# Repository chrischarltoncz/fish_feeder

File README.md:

# fish_feeder

This is the python code to run the pneumatic fish feeder system which functions as follows:

The food is placed in a clear plastic cylinder/hopper. There is an illumination LED strip to light it up on one side. A Pi camera on the opposite side to capture images of the tube and the food. This image will be used for tracking food consumption and level.

The base of the tube has the main feeder body, this incorporates a delrin screw drive to move the food. The screw is rotated via at NEMA17 motor at one end, at the opposite end is an opto sensor and a 6 slot chopper for counting the rotations. This is used to confirm the rotation happens and the motor is not jammed.

The thread deposits the food into a conical volume, this funnels it down to a fitting where it exits the food hopper body/assembly. Above the conical volume is mounted an air solenoid valve, it is fed via 22-25psi house air. The air supply is split off via a needle valve to supply a small continuous stream of air that travels to the bulk food.
This is to keep it dry, it also passes over a temperature and humidity sensor to record the values, this ensures the food is always exposed to dry air and if there is an air supply problem it can be flagged.

Currently (Jan 2025) the air solenoid is turned on prior to the food loading screw rotation, this is to equalize the pressure along the various parts (thread/hopper) so fine powdered food does not flow and collect/jam the screw mech.

Once the food passes out of the food hopper mech, it passes to the rotary valve mechanism.

There is a curved interface tube which is centrally located and passes to near the circumference of a rotating disc, this disc has embedded magnets which lightly clamp the rotor to the stator, the stator underneath has 30X fittings which correspond to each fish tank. 

The rotor is turned via a belt which is in turn rotated via a NEMA23 stepper motor. A home sensor microswitch is stationary on the main feeder assembly, it activates via a 3D printed bump which is VHB taped to the rotor. There is a well defined number of microsteps between home and port 1 so the system can home and index to the correct port location.

One each feeding cycle the rotor is re-homed, then indexed to port 1. Prior to food loading the tank/port is air dried for a number of seconds (typically 60-75) to dry the end of the tube to avoid wet food. 

Links:

Stepper motor drive boards:
https://www.allmotion.com/ezhr17en

Onshape design:
[https://www.allmotion.com/ezhr17en
](https://cad.onshape.com/documents/b092e7b6adc17bd3a3390fe1/w/5d2cf434299dfa3fc55c8225/e/223d4cf3e3f1612e807b6f1d?renderMode=0&uiState=6785ac46c4b3921eef4992e4)

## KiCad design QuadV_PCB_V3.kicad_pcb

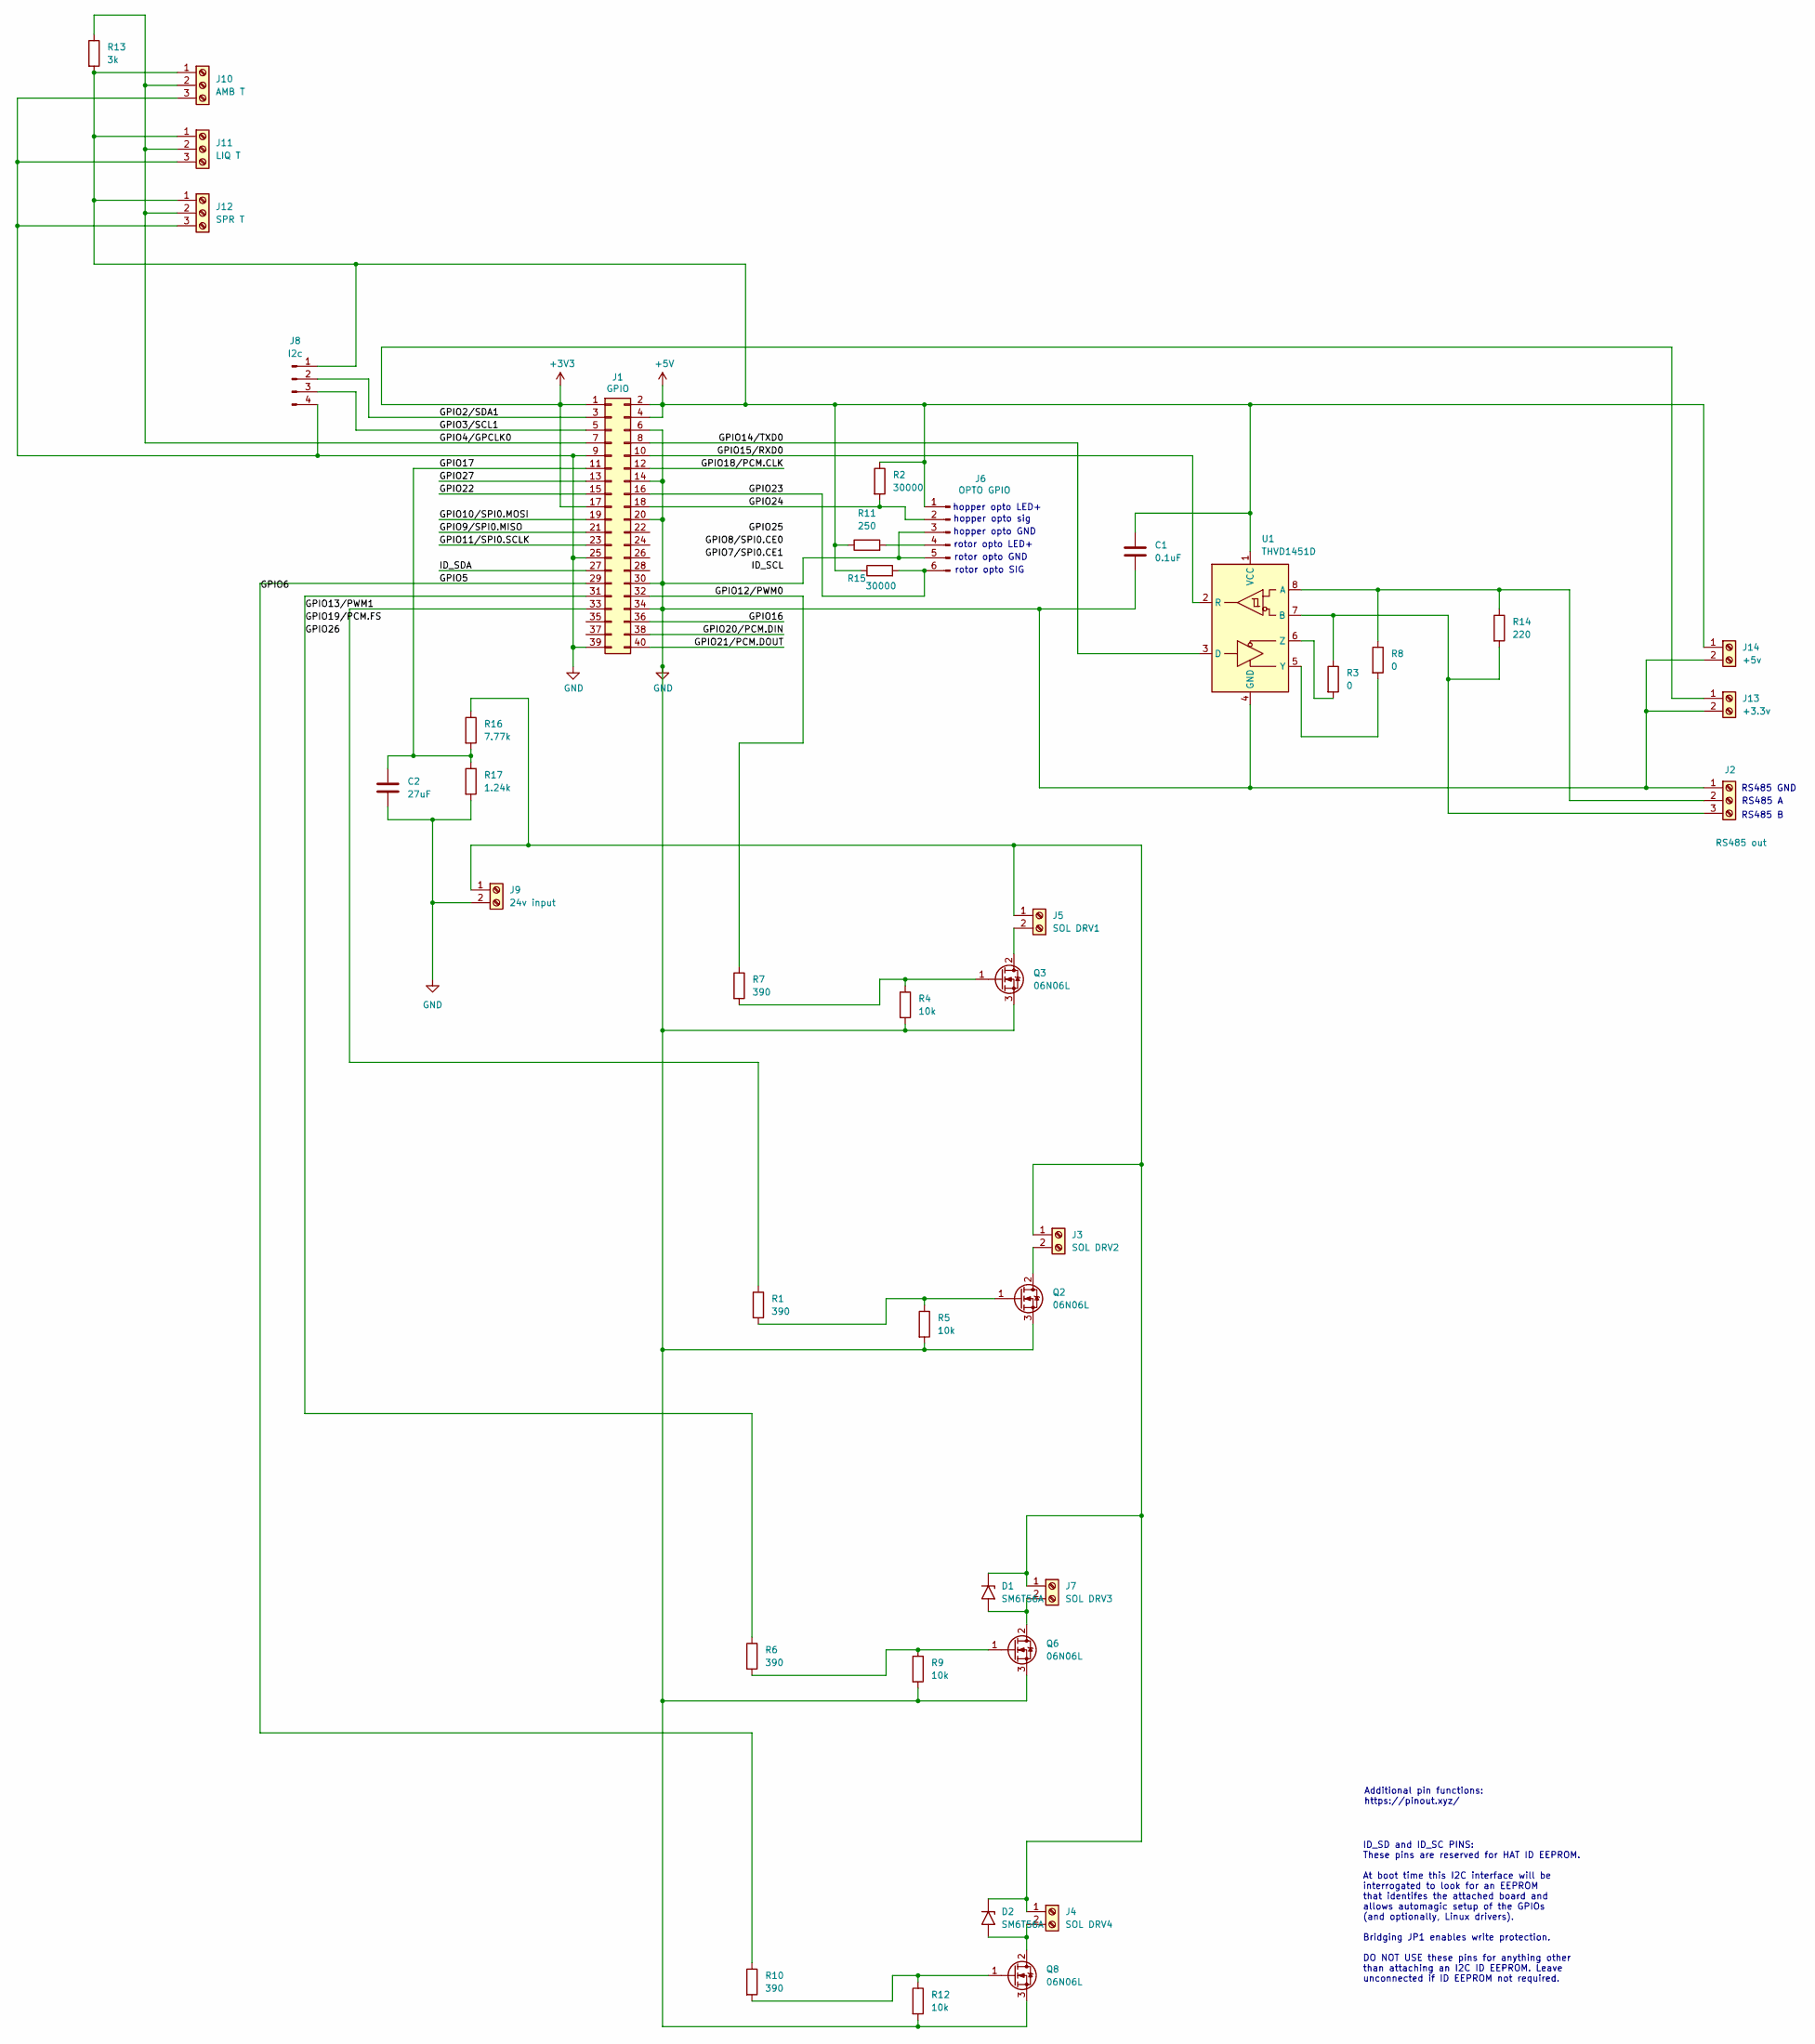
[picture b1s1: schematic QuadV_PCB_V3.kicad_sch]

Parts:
C1: 0.1uF; C_0201_0603Metric
C2: 27uF; CP_Elec_6.3x5.9
D1, D2: SM6T56A; D_SMB
J1: GPIO; PinSocket_2x20_P2.54mm_Vertical
J2: RS485 out; TerminalBlock_Xinya_XY308-2.54-3P_1x03_P2.54mm_Horizontal
J3: SOL DRV2; TerminalBlock_bornier-2_P5.08mm
J4: SOL DRV4; TerminalBlock_bornier-2_P5.08mm
J5: SOL DRV1; TerminalBlock_bornier-2_P5.08mm
J6: OPTO GPIO; Molex_KK-254_AE-6410-06A_1x06_P2.54mm_Vertical
J7: SOL DRV3; TerminalBlock_bornier-2_P5.08mm
J8: I2c; Molex_KK-254_AE-6410-04A_1x04_P2.54mm_Vertical
J9: 24v input; TerminalBlock_Phoenix_MKDS-1,5-2-5.08_1x02_P5.08mm_Horizont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
J10: AMB T; TerminalBlock_Xinya_XY308-2.54-3P_1x03_P2.54mm_Horizontal
J11: LIQ T; TerminalBlock_Xinya_XY308-2.54-3P_1x03_P2.54mm_Horizontal
J12: SPR T; TerminalBlock_Xinya_XY308-2.54-3P_1x03_P2.54mm_Horizontal
J13: +3.3v; TerminalBlock_Xinya_XY308-2.54-2P_1x02_P2.54mm_Horizontal
J14: +5v; TerminalBlock_Xinya_XY308-2.54-2P_1x02_P2.54mm_Horizontal
Q2, Q3, Q6, Q8: 06N06L; SOT-23-3
R1, R6, R7, R10: 390; R_0603_1608Metric
R2, R15: 30000; R_0603_1608Metric
R3, R8: 0; R_0603_1608Metric
R4, R5, R9, R12: 10k; R_0603_1608Metric
R11: 250; R_0603_1608Metric
R13: 3k; R_0603_1608Metric
R14: 220; R_0603_1608Metric
R16: 7.77k; R_0603_1608Metric
R17: 1.24k; R_0603_1608Metric
U1: THVD1451D; SOIC-8_3.9x4.9mm_P1.27mm

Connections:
+3V3: J1.1, J1.17, J13.1
+5V: C1.1, J1.2, J1.4, J6.1, J8.1, J10.1, J11.1, J12.1, J14.1, R2.1, R11.1, R13.2, R15.1, U1.1 (VCC)
/GPIO2/SDA1: J1.3, J8.2
/GPIO3/SCL1: J1.5, J8.3
/GPIO4/GPCLK0: J1.7, J10.2, J11.2, J12.2, R13.1
/GPIO5: J1.29, R10.1
/GPIO9/SPI0.MISO: J1.21
/GPIO10/SPI0.MOSI: J1.19
/GPIO11/SPI0.SCLK: J1.23
/GPIO12/PWM0: J1.32, R7.1
/GPIO13/PWM1: J1.31, R6.1
/GPIO14/TXD0: J1.8, U1.3 (D)
/GPIO15/RXD0: J1.10, U1.2 (R)
/GPIO16: J1.36
/GPIO17: C2.1, J1.11, R16.2, R17.1
/GPIO18/PCM.CLK: J1.12
/GPIO20/PCM.DIN: J1.38
/GPIO21/PCM.DOUT: J1.40
/GPIO22: J1.15
/GPIO23: J1.16, J6.6, R15.2
/GPIO24: J1.18, J6.2, R2.2
/GPIO27: J1.13
/ID_SDA: J1.27
GND: C1.2, C2.2, J1.6, J1.9, J1.14, J1.20, J1.25, J1.30, J1.34, J1.39, J2.1, J6.3, J6.5, J8.4, J9.2, J10.3, J11.3, J12.3, J13.2, J14.2, Q2.3 (S), Q3.3 (S), Q6.3 (S), Q8.3 (S), R4.2, R5.2, R9.2, R12.2, R17.2, U1.4 (GND)
unnamed: D1.1 (A1), D2.1 (A1), J3.1, J4.1, J5.1, J7.1, J9.1, R16.1
unnamed: D1.2 (A2), J7.2, Q6.2 (D)
unnamed: D2.2 (A2), J4.2, Q8.2 (D)
unnamed: J1.33, R1.1
unnamed: J2.2, R8.1, R14.1, U1.8 (A)
unnamed: J2.3, R3.1, R14.2, U1.7 (B)
unnamed: J3.2, Q2.2 (D)
unnamed: J5.2, Q3.2 (D)
unnamed: J6.4, R11.2
unnamed: Q2.1 (G), R1.2, R5.1
unnamed: Q3.1 (G), R4.1, R7.2
unnamed: Q6.1 (G), R6.2, R9.1
unnamed: Q8.1 (G), R10.2, R12.1
unnamed: R8.2, U1.5 (Y)
unnamed: R3.2, U1.6 (Z)

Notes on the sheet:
Additional pin functions: https://pinout.xyz/
hopper opto GND
RS485 GND
RS485 A
ID_SD and ID_SC PINS: These pins are reserved for HAT ID EEPROM. At boot time this I2C interface will be interrogated to look for an EEPROM that identifes the attached board and allows automagic setup of the GPIOs (and optionally, Linux drivers). Bridging JP1 enables write protection. DO NOT USE th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
RS485 B
rotor opto LED+
rotor opto SIG
hopper opto sig
hopper opto LED+
rotor opto GND

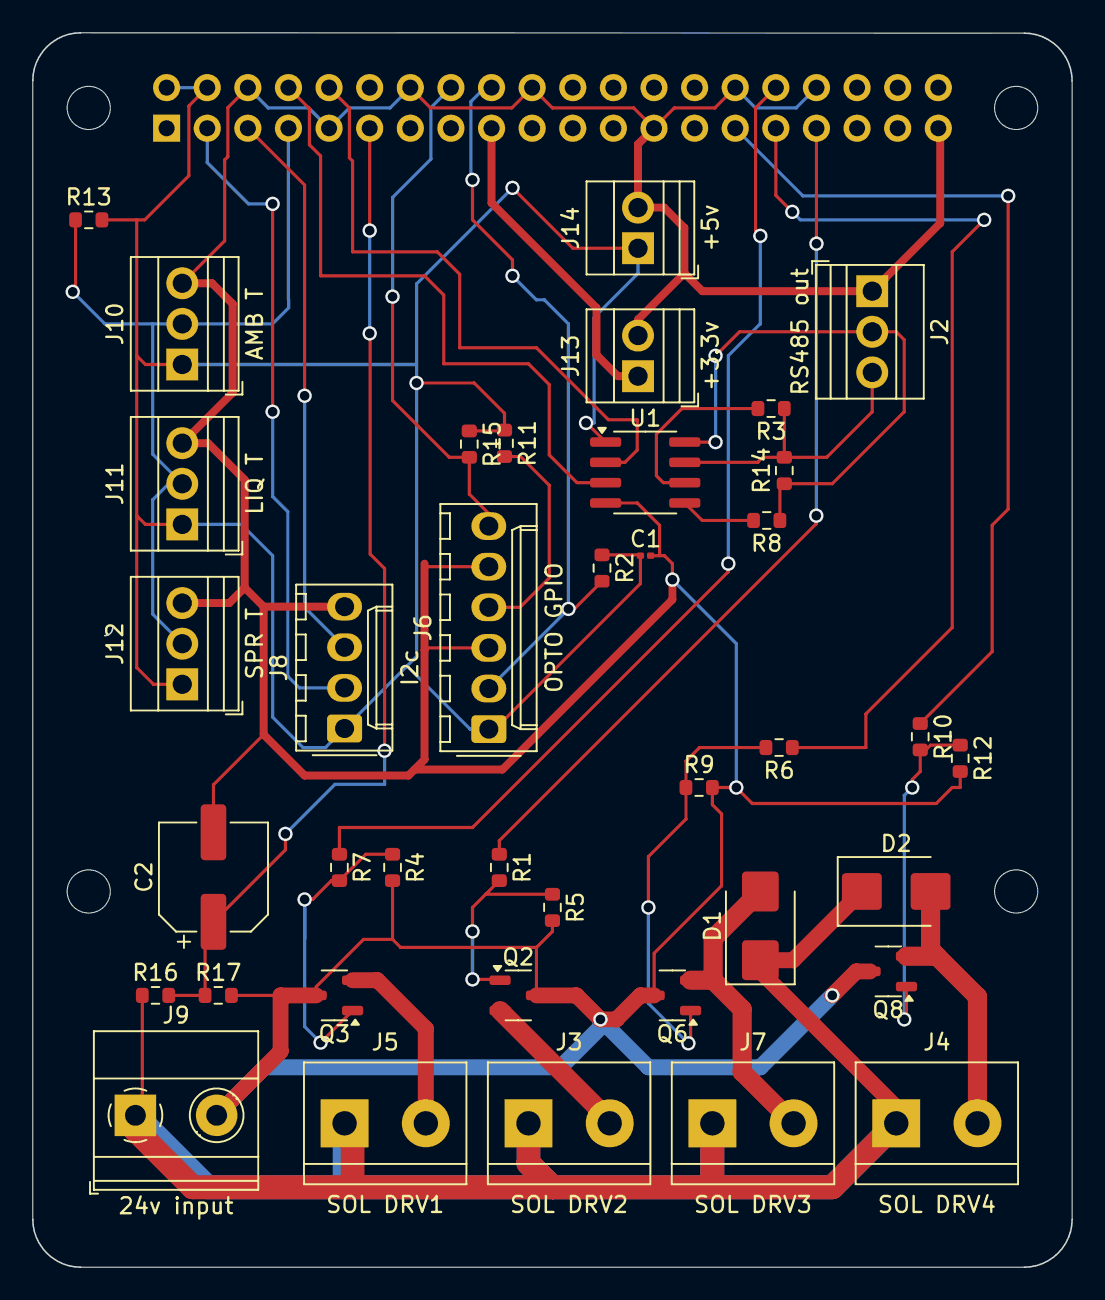
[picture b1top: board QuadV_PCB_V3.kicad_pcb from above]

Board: 2 copper layers, 65.0 x 77.2 mm, 44 parts (1 on the bottom side), 29 nets.

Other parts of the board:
MH1, MH2, MH3, MH4: MountingHole_2.7mm_M2.5

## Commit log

2025-01-13 Add files via upload
    Fish feeder and quadravision PCB KiCAD files Version 3 (jan 2025)
2025-01-14 Add files via upload
    Capture image using Pi camera, output a level based off the image of food
2025-01-30 This version has the changes for the 3:1 gears
    3:1 gearbox scale changes and motor speeds, also extension to 30 days for a longer test
2025-08-06 Add files via upload
    Version has feature to read in a text file to define the amount of food to send to each tank
2025-08-08 Add files via upload
    # Rev22 adjusted the loop timer for hopper loading. Added extra loop time and adjusted the loop delay from 0.02 to 0.01 seconds. Also added a while loop if the state is TRUE when the timer starts wai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
    # added global exception handler to send slack if the code crashes anytime
    # this should be fixed: fix the hopper screw slot count, it still counts wrong sometimes (6.22?) should be 0.99 to 1 normally
    # Rev23 report the hopper screw ratio in slack, the minimum ratio during the whole feeding cycle. Can now have zero values in the food quantity text file and it will just skip those and send no food
    # Rev24 if there is less than 5
2025-08-11 Add files via upload
    This is Rev24 but with bugs fixed
2025-08-11 Add files via upload
    rev25 with web hook removed
2026-05-18 Add files via upload
    Major release for the V2.0 feeder. Used for the hotel install and testing
